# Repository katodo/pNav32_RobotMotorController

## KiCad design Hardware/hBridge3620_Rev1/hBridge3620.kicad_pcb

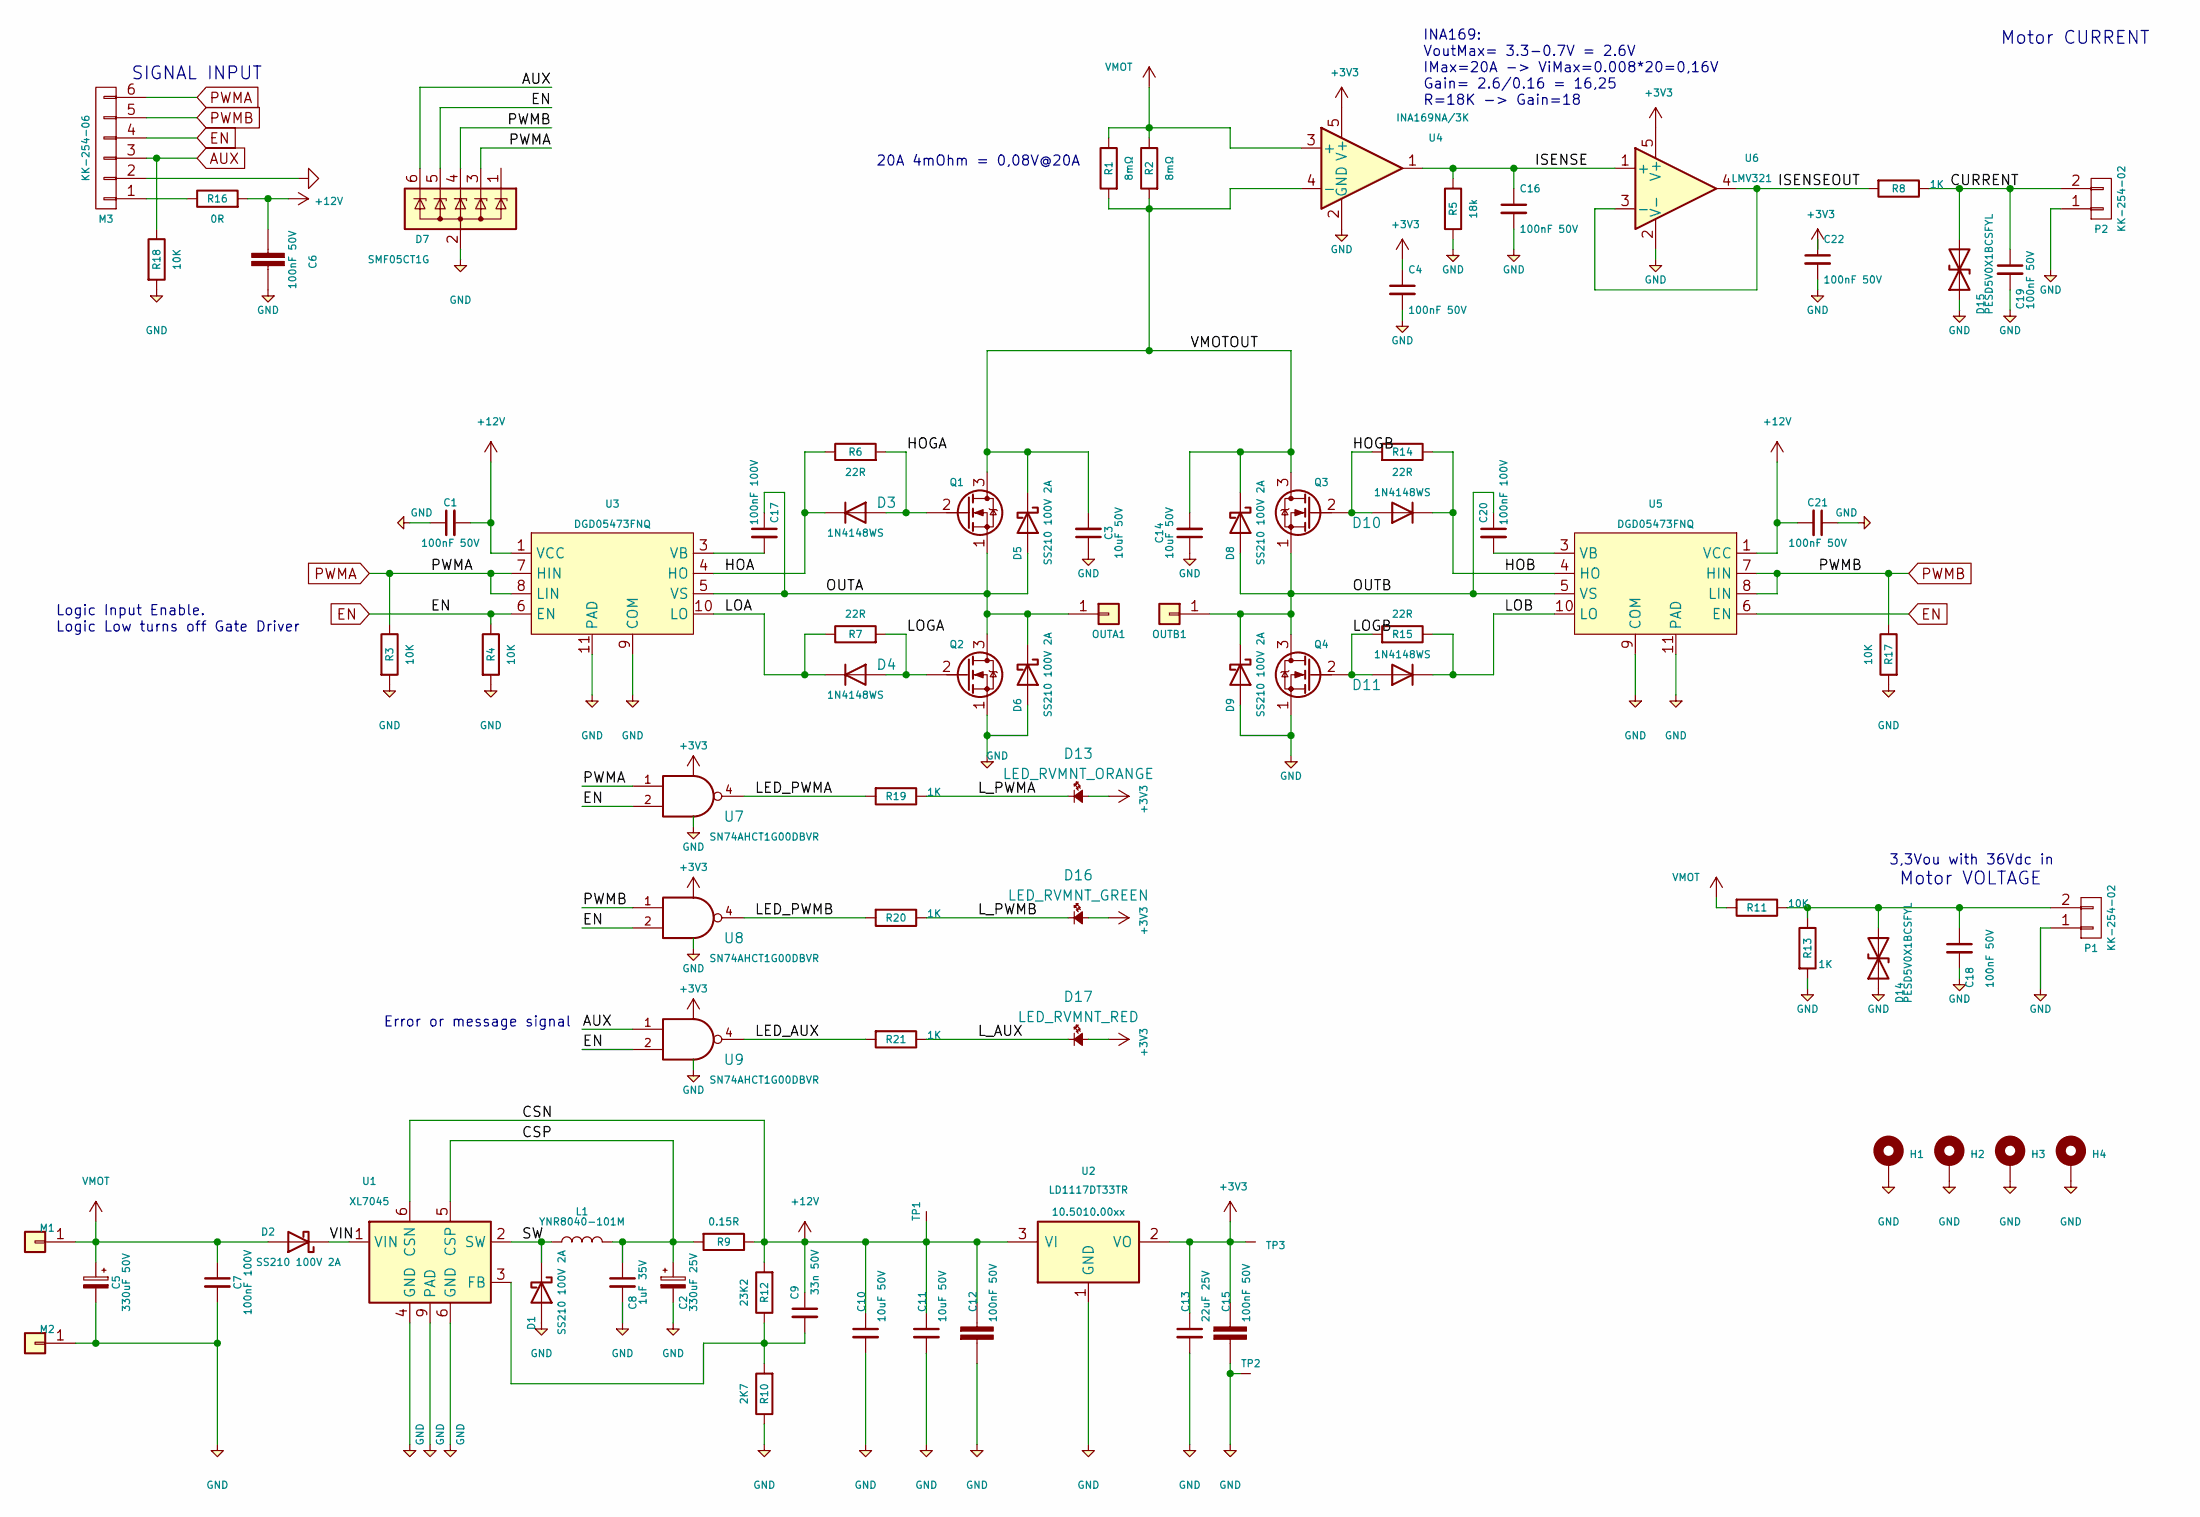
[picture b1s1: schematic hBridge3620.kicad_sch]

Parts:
C1, C4, C6, C12, C15, C16, C18, C19, C21, C22: 100nF 50V; C_0603_1608Metric; LCSC C14663
C2: 330uF 25V; CP_Radial_D10.0mm_P5.00mm
C3, C10, C11, C14: 10uF 50V; C_1206_3216Metric_Pad1.33x1.80mm_HandSolder; LCSC C13585
C5: 330uF 50V; CP_Radial_D12.5mm_P5.00mm
C7, C17, C20: 100nF 100V; C_0805_2012Metric; LCSC C28233
C8: 1uF 35V; C_0805_2012Metric; LCSC C28323
C9: 33n 50V; C_0603_1608Metric; LCSC C21117
C13: 22uF 25V; C_1206_3216Metric_Pad1.33x1.80mm_HandSolder; LCSC C12891
D1, D2, D5, D6, D8, D9: SS210 100V 2A; D_SMA; LCSC C14996
D3, D4, D10, D11: 1N4148WS; D_SOD-323; LCSC C2128
D7: SMF05CT1G; SOT-363_SC-70-6; LCSC C15879
D13: LED_RVMNT_ORANGE; LED_1206_3216Metric_ReverseMount_Hole1.8x2.4mm; MOUSER 859-LTST-C230KFKT
D14, D15: PESD5V0X1BCSFYL; D_0603_1608Metric; LCSC C2443412
D16: LED_RVMNT_GREEN; LED_1206_3216Metric_ReverseMount_Hole1.8x2.4mm; MOUSER 859-LTST-C230KGKT
D17: LED_RVMNT_RED; LED_1206_3216Metric_ReverseMount_Hole1.8x2.4mm; MOUSER 859-LTST-C230KRKT
H1, H2, H3, H4: MountingHole_Pad; MountingHole_3.2mm_M3_Pad_Via
L1: YNR8040-101M; L_Taiyo-Yuden_NR-80xx; LCSC C341083
M1, M2: HIGHCURRENTPAD2; SolderWire-2.5sqmm_1x01_D2.4mm_OD4.4mm
M3: KK-254-06; Molex_KK-254_AE-6410-06A_1x06_P2.54mm_Vertical
OUTA1: HIGHCURRENTPAD2; SolderWire-2.5sqmm_1x01_D2.4mm_OD4.4mm
OUTB1: HIGHCURRENTPAD2; SolderWire-2.5sqmm_1x01_D2.4mm_OD4.4mm
P1, P2: KK-254-02; Molex_KK-254_AE-6410-02A_1x02_P2.54mm_Vertical
Q1, Q2, Q3, Q4: RU6888M; DFN-8-1EP_5.55x5.2mm_P1.27mm_EP4.12x4.6mm_MOSFET_3PIN; LCSC C180959
R1, R2: 8mΩ; R_2512_6332Metric; LCSC C469375
R3, R4, R11, R17, R18: 10K; R_0603_1608Metric; LCSC C25804
R5: 18k; R_0603_1608Metric; LCSC C25810
R6, R7, R14, R15: 22R; R_0603_1608Metric; LCSC C23345
R8, R13, R19, R20, R21: 1K; R_0603_1608Metric; LCSC C21190
R9: 0.15R; R_1206_3216Metric; LCSC C37936
R10: 2K7; R_0603_1608Metric; LCSC C13167
R12: 23K2; R_0603_1608Metric; LCSC C2930078
R16: 0R; R_0603_1608Metric; LCSC C21189
TP1, TP2, TP3: TESTPAD; TestPoint_Pad_2.5x2.5mm
U1: XL7045; SOIC-8-1EP_3.9x4.9mm_P1.27mm_EP2.29x3mm; LCSC C126474
U2: LD1117DT33TR; TO-252-2; LCSC C36395
U3, U5: DGD05473FNQ; U-DFN3030-10_3.1x3.1mm_P0.5mm_EP1.8x2.6mm_ThermalVias; LCSC C2677131
U4: INA169NA/3K; SOT-23-5; LCSC C44322
U6: LMV321; SOT-23-5; LCSC C7972
U7, U8, U9: SN74AHCT1G00DBVR; SOT-23-5; LCSC C473380

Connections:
+3V3: C4.1, C13.1, C15.1, C22.1, D13.2, D16.2, D17.2, TP3.1 (TP), U2.2 (VO), U4.5 (V+), U6.5 (V+), U7.5 (VCC), U8.5 (VCC), U9.5 (VCC)
/CSP: C2.1, C8.1, L1.2, R9.2, U1.5 (CSP)
/CURRENT: C19.1, D15.2 (A2), P2.2, R8.1
/HOA: D3.1 (K), R6.1, U3.4 (HO)
/HOB: D10.1 (K), R14.1, U5.4 (HO)
/HOGA: D3.2 (A), Q1.2 (G), R6.2
/HOGB: D10.2 (A), Q3.2 (G), R14.2
/ISENSE: C16.1, R5.1, U4.1, U6.1 (+)
/ISENSEOUT: R8.2, U6.3 (-), U6.4
/LED_AUX: R21.2, U9.4
/LED_PWMA: R19.2, U7.4
/LED_PWMB: R20.2, U8.4
/LOA: D4.1 (K), R7.1, U3.10 (LO)
/LOB: D11.1 (K), R15.1, U5.10 (LO)
/LOGA: D4.2 (A), Q2.2 (G), R7.2
/LOGB: D11.2 (A), Q4.2 (G), R15.2
/L_AUX: D17.1, R21.1
/L_PWMA: D13.1, R19.1
/L_PWMB: D16.1, R20.1
/OUTA: C17.1, D5.2 (A), D6.1 (K), OUTA1.1, Q1.1 (S), Q2.3 (D), U3.5 (VS)
/OUTB: C20.1, D8.2 (A), D9.1 (K), OUTB1.1, Q3.1 (S), Q4.3 (D), U5.5 (VS)
/SW: D1.1 (K), L1.1, U1.2 (SW)
/VIN: D2.1 (K), U1.1 (VIN)
/VMOTOUT: C3.2, C14.2, D5.1 (K), D8.1 (K), Q1.3 (D), Q3.3 (D), R1.2, R2.2, U4.4 (-)
AUX: D7.6 (K), M3.3, R18.1, U9.1
EN: D7.5 (K), M3.4, R4.1, U3.6 (EN), U5.6 (EN), U7.2, U8.2, U9.2
unnamed: C9.2, R10.2, R12.1, U1.3 (FB)
unnamed: C17.2, U3.3 (VB)
unnamed: C18.1, D14.2 (A2), P1.2, R11.1, R13.1
unnamed: C20.2, U5.3 (VB)
unnamed: M3.1, R16.1
PWMA: D7.3 (K), M3.6, R3.1, U3.7 (HIN), U3.8 (LIN), U7.1
PWMB: D7.4 (K), M3.5, R17.1, U5.7 (HIN), U5.8 (LIN), U8.1
VMOT: C5.1, C7.1, D2.2 (A), M1.1, R1.1, R2.1, R11.2, U4.3 (+)

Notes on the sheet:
3,3Vou with 36Vdc in
Logic Input Enable. Logic Low turns off Gate Driver
Motor VOLTAGE
Motor CURRENT
20A 4mOhm = 0,08V@20A
INA169: VoutMax= 3.3-0.7V = 2.6V IMax=20A -> ViMax=0.008*20=0,16V Gain= 2.6/0.16 = 16,25 R=18K -> Gain=18
Error or message signal
SIGNAL INPUT

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
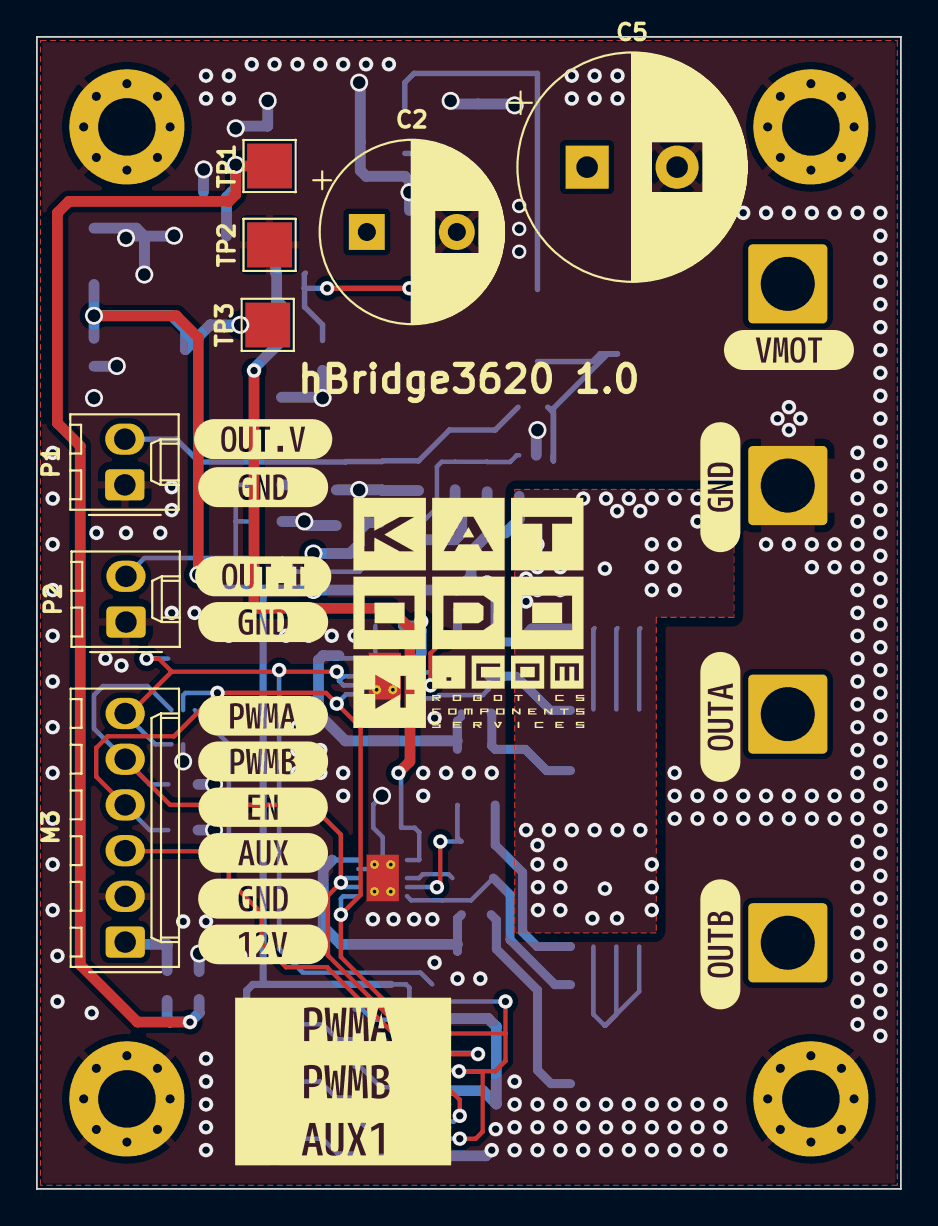
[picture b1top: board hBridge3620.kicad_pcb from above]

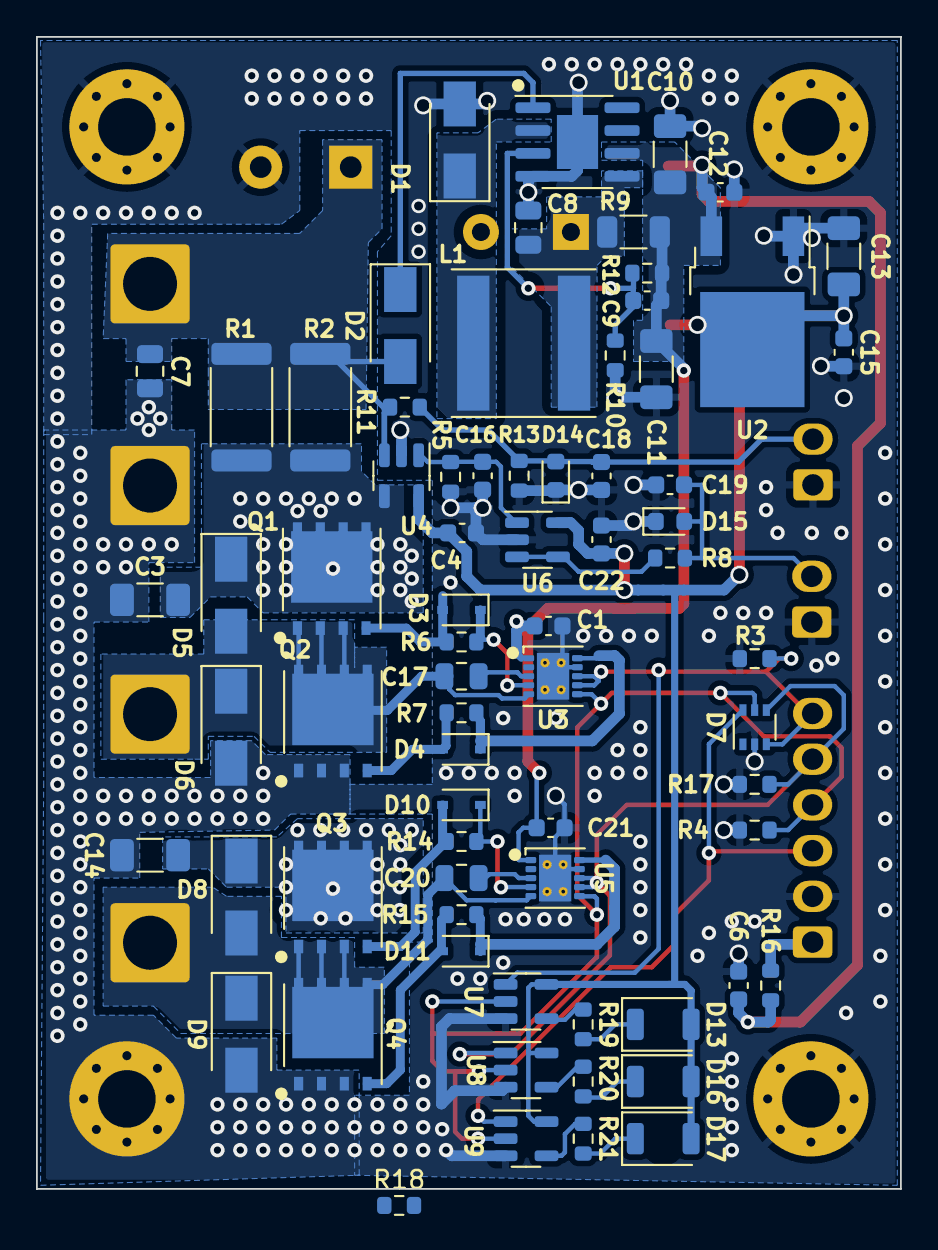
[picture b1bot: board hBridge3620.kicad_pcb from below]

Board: 2 copper layers, 48.0 x 64.0 mm, 102 parts (71 on the bottom side), 36 nets.

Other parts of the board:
kibuzzard-63AF517B: G***; kibuzzard-63AF517B
kibuzzard-63AF5189: G***; kibuzzard-63AF5189
kibuzzard-63B18A56: G***; kibuzzard-63B18A56
kibuzzard-63B18C51: G***; kibuzzard-63B18C51
kibuzzard-63B18C79: G***; kibuzzard-63B18C79
kibuzzard-63B18C86: G***; kibuzzard-63B18C86
kibuzzard-63B83704: G***; kibuzzard-63B83704
kibuzzard-63934BD9, kibuzzard-63934BD9#2, kibuzzard-63934BD9#3: G***; kibuzzard-63934BD9
kibuzzard-6393473F: G***; kibuzzard-6393473F
kibuzzard-63934735: G***; kibuzzard-63934735
kibuzzard-63934749: G***; kibuzzard-63934749
kibuzzard-63934750: G***; kibuzzard-63934750
kibuzzard-63934760: G***; kibuzzard-63934760

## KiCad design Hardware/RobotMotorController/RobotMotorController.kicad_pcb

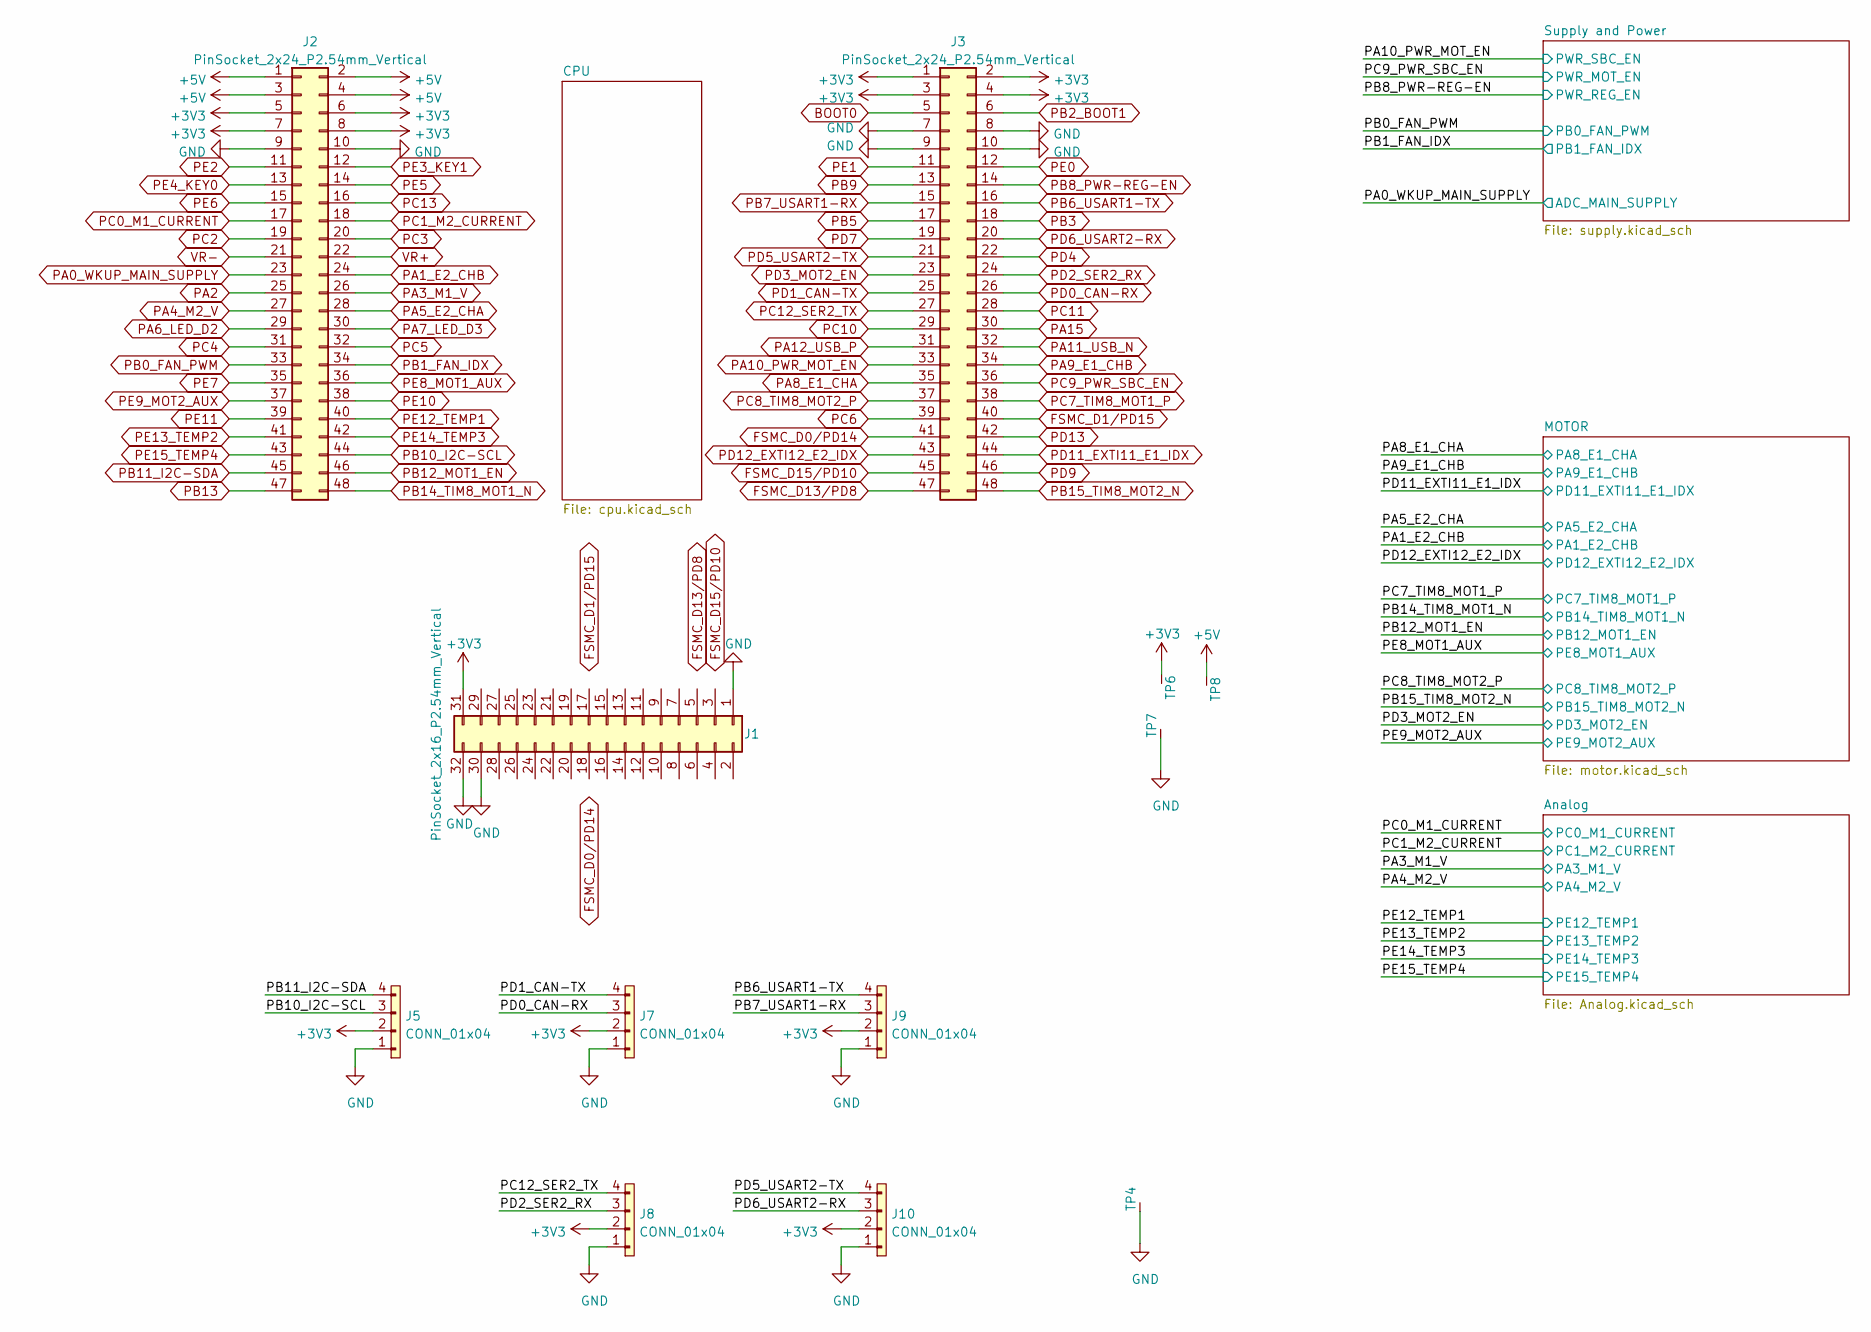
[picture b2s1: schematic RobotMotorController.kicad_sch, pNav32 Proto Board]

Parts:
J1: PinSocket_2x16_P2.54mm_Vertical
J2, J3: PinSocket_2x24_P2.54mm_Vertical
J5, J7, J8, J9, J10: CONN_01x04; Molex_KK-254_AE-6410-04A_1x04_P2.54mm_Vertical
TP4, TP6, TP7, TP8: TESTPAD; TestPoint_Loop_D2.50mm_Drill1.85mm

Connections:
+3V3: J1.31, J2.5, J2.6, J2.7, J2.8, J3.1, J3.2, J3.3, J3.4, J5.2, J7.2, J8.2, J9.2, J10.2, TP6.1 (TP); also elsewhere on the board
+5V: J2.1, J2.2, J2.3, J2.4, TP8.1 (TP); also elsewhere on the board
BOOT0: J3.5
FSMC_D0/PD14: J3.41
FSMC_D1/PD15: J3.40
FSMC_D13/PD8: J3.47
FSMC_D15/PD10: J3.45
PA0_WKUP_MAIN_SUPPLY: J2.23; also elsewhere on the board
PA1_E2_CHB: J2.24; also elsewhere on the board
PA2: J2.25
PA3_M1_V: J2.26; also elsewhere on the board
PA4_M2_V: J2.27; also elsewhere on the board
PA5_E2_CHA: J2.28; also elsewhere on the board
PA6_LED_D2: J2.29
PA7_LED_D3: J2.30
PA8_E1_CHA: J3.35; also elsewhere on the board
PA9_E1_CHB: J3.34; also elsewhere on the board
PA10_PWR_MOT_EN: J3.33; also elsewhere on the board
PA11_USB_N: J3.32
PA12_USB_P: J3.31
PA15: J3.30
PB0_FAN_PWM: J2.33; also elsewhere on the board
PB1_FAN_IDX: J2.34; also elsewhere on the board
PB2_BOOT1: J3.6
PB3: J3.18
PB5: J3.17
PB6_USART1-TX: J3.16, J9.4
PB7_USART1-RX: J3.15, J9.3
PB8_PWR-REG-EN: J3.14; also elsewhere on the board
PB9: J3.13
PB10_I2C-SCL: J2.44, J5.3
PB11_I2C-SDA: J2.45, J5.4
PB12_MOT1_EN: J2.46; also elsewhere on the board
PB13: J2.47
PB14_TIM8_MOT1_N: J2.48; also elsewhere on the board
PB15_TIM8_MOT2_N: J3.48; also elsewhere on the board
PC0_M1_CURRENT: J2.17; also elsewhere on the board
PC1_M2_CURRENT: J2.18; also elsewhere on the board
PC2: J2.19
PC3: J2.20
PC4: J2.31
PC5: J2.32
PC6: J3.39
PC7_TIM8_MOT1_P: J3.38; also elsewhere on the board
PC8_TIM8_MOT2_P: J3.37; also elsewhere on the board
PC9_PWR_SBC_EN: J3.36; also elsewhere on the board
PC10: J3.29
PC11: J3.28
PC12_SER2_TX: J3.27, J8.4
PC13: J2.16
PD0_CAN-RX: J3.26, J7.3
PD1_CAN-TX: J3.25, J7.4
PD2_SER2_RX: J3.24, J8.3
PD3_MOT2_EN: J3.23; also elsewhere on the board
PD4: J3.22
PD5_USART2-TX: J3.21, J10.4
PD6_USART2-RX: J3.20, J10.3
PD7: J3.19
PD9: J3.46
PD11_EXTI11_E1_IDX: J3.44; also elsewhere on the board
PD12_EXTI12_E2_IDX: J3.43; also elsewhere on the board
PD13: J3.42
PE0: J3.12
PE1: J3.11
PE2: J2.11
PE3_KEY1: J2.12
PE4_KEY0: J2.13
PE5: J2.14
PE6: J2.15
PE7: J2.35
PE8_MOT1_AUX: J2.36; also elsewhere on the board
PE9_MOT2_AUX: J2.37; also elsewhere on the board
PE10: J2.38
PE11: J2.39
PE12_TEMP1: J2.40; also elsewhere on the board
PE13_TEMP2: J2.41; also elsewhere on the board
PE14_TEMP3: J2.42; also elsewhere on the board
PE15_TEMP4: J2.43; also elsewhere on the board
VR+: J2.22
VR-: J2.21

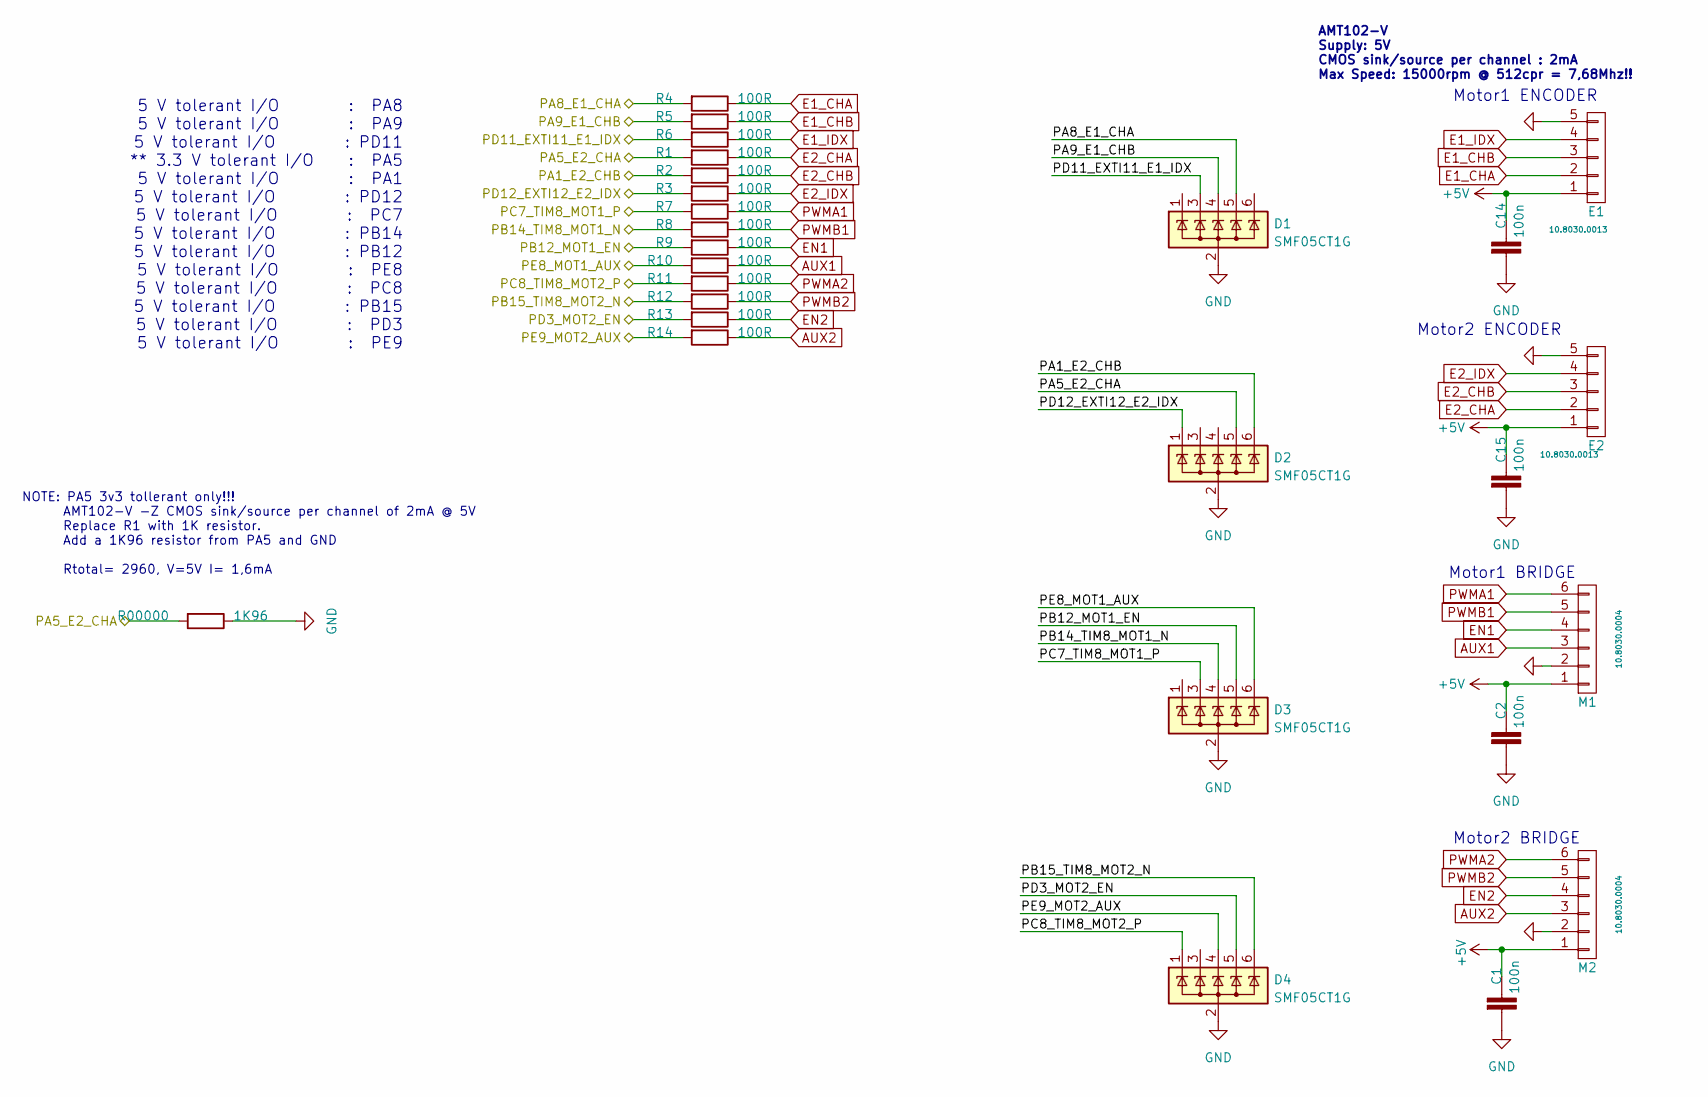
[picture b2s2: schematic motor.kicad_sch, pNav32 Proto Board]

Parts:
C1, C2, C14, C15: 100n; C_0603_1608Metric; LCSC C14663
D1, D2, D3, D4: SMF05CT1G; SOT-363_SC-70-6; LCSC C15879
E1, E2: Molex_KK-254_AE-6410-05A_1x05_P2.54mm_Vertical
M1, M2: Molex_KK-254_AE-6410-06A_1x06_P2.54mm_Vertical
R00000: 1K96; R_0603_1608Metric; LCSC C227664
R1: 100R; R_0603_1608Metric; LCSC C21190
R2, R3, R4, R5, R6, R7, R8, R9, R10, R11, R12, R13, R14: 100R; R_0603_1608Metric; LCSC C22775

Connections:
+5V: C1.1, C2.1, C14.1, C15.1, E1.1, E2.1, M1.1, M2.1; also elsewhere on the board
AUX1: M1.3, R10.1
AUX2: M2.3, R14.1
E1_CHA: E1.2, R4.1
E1_CHB: E1.3, R5.1
E1_IDX: E1.4, R6.1
E2_CHA: E2.2, R1.1
E2_CHB: E2.3, R2.1
E2_IDX: E2.4, R3.1
EN1: M1.4, R9.1
EN2: M2.4, R13.1
PA1_E2_CHB: D2.6 (K), R2.2; also elsewhere on the board
PA5_E2_CHA: D2.5 (K), R00000.2, R1.2; also elsewhere on the board
PA8_E1_CHA: D1.5 (K), R4.2; also elsewhere on the board
PA9_E1_CHB: D1.4 (K), R5.2; also elsewhere on the board
PB12_MOT1_EN: D3.5 (K), R9.2; also elsewhere on the board
PB14_TIM8_MOT1_N: D3.4 (K), R8.2; also elsewhere on the board
PB15_TIM8_MOT2_N: D4.6 (K), R12.2; also elsewhere on the board
PC7_TIM8_MOT1_P: D3.3 (K), R7.2; also elsewhere on the board
PC8_TIM8_MOT2_P: D4.1 (K), R11.2; also elsewhere on the board
PD3_MOT2_EN: D4.5 (K), R13.2; also elsewhere on the board
PD11_EXTI11_E1_IDX: D1.3 (K), R6.2; also elsewhere on the board
PD12_EXTI12_E2_IDX: D2.1 (K), R3.2; also elsewhere on the board
PE8_MOT1_AUX: D3.6 (K), R10.2; also elsewhere on the board
PE9_MOT2_AUX: D4.4 (K), R14.2; also elsewhere on the board
PWMA1: M1.6, R7.1
PWMA2: M2.6, R11.1
PWMB1: M1.5, R8.1
PWMB2: M2.5, R12.1

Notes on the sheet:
Motor1 ENCODER
Motor2 ENCODER
Motor2 BRIDGE
5 V tolerant I/O : PA8 5 V tolerant I/O : PA9 5 V tolerant I/O : PD11 ** 3.3 V tolerant I/O : PA5 5 V tolerant I/O : PA1 5 V tolerant I/O : PD12 5 V tolerant I/O : PC7 5 V tolerant I/O : PB14 5 V tolerant I/O : PB12 5 V tolerant I/O : PE8 5 V tolerant I/O : PC8 5 V tolerant I/O : PB15 5 V tolerant 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
NOTE: PA5 3v3 tollerant only!!! AMT102-V -Z CMOS sink/source per channel of 2mA @ 5V Replace R1 with 1K resistor. Add a 1K96 resistor from PA5 and GND Rtotal= 2960, V=5V I= 1,6mA
Motor1 BRIDGE
AMT102-V Supply: 5V CMOS sink/source per channel : 2mA Max Speed: 15000rpm @ 512cpr = 7,68Mhz!!

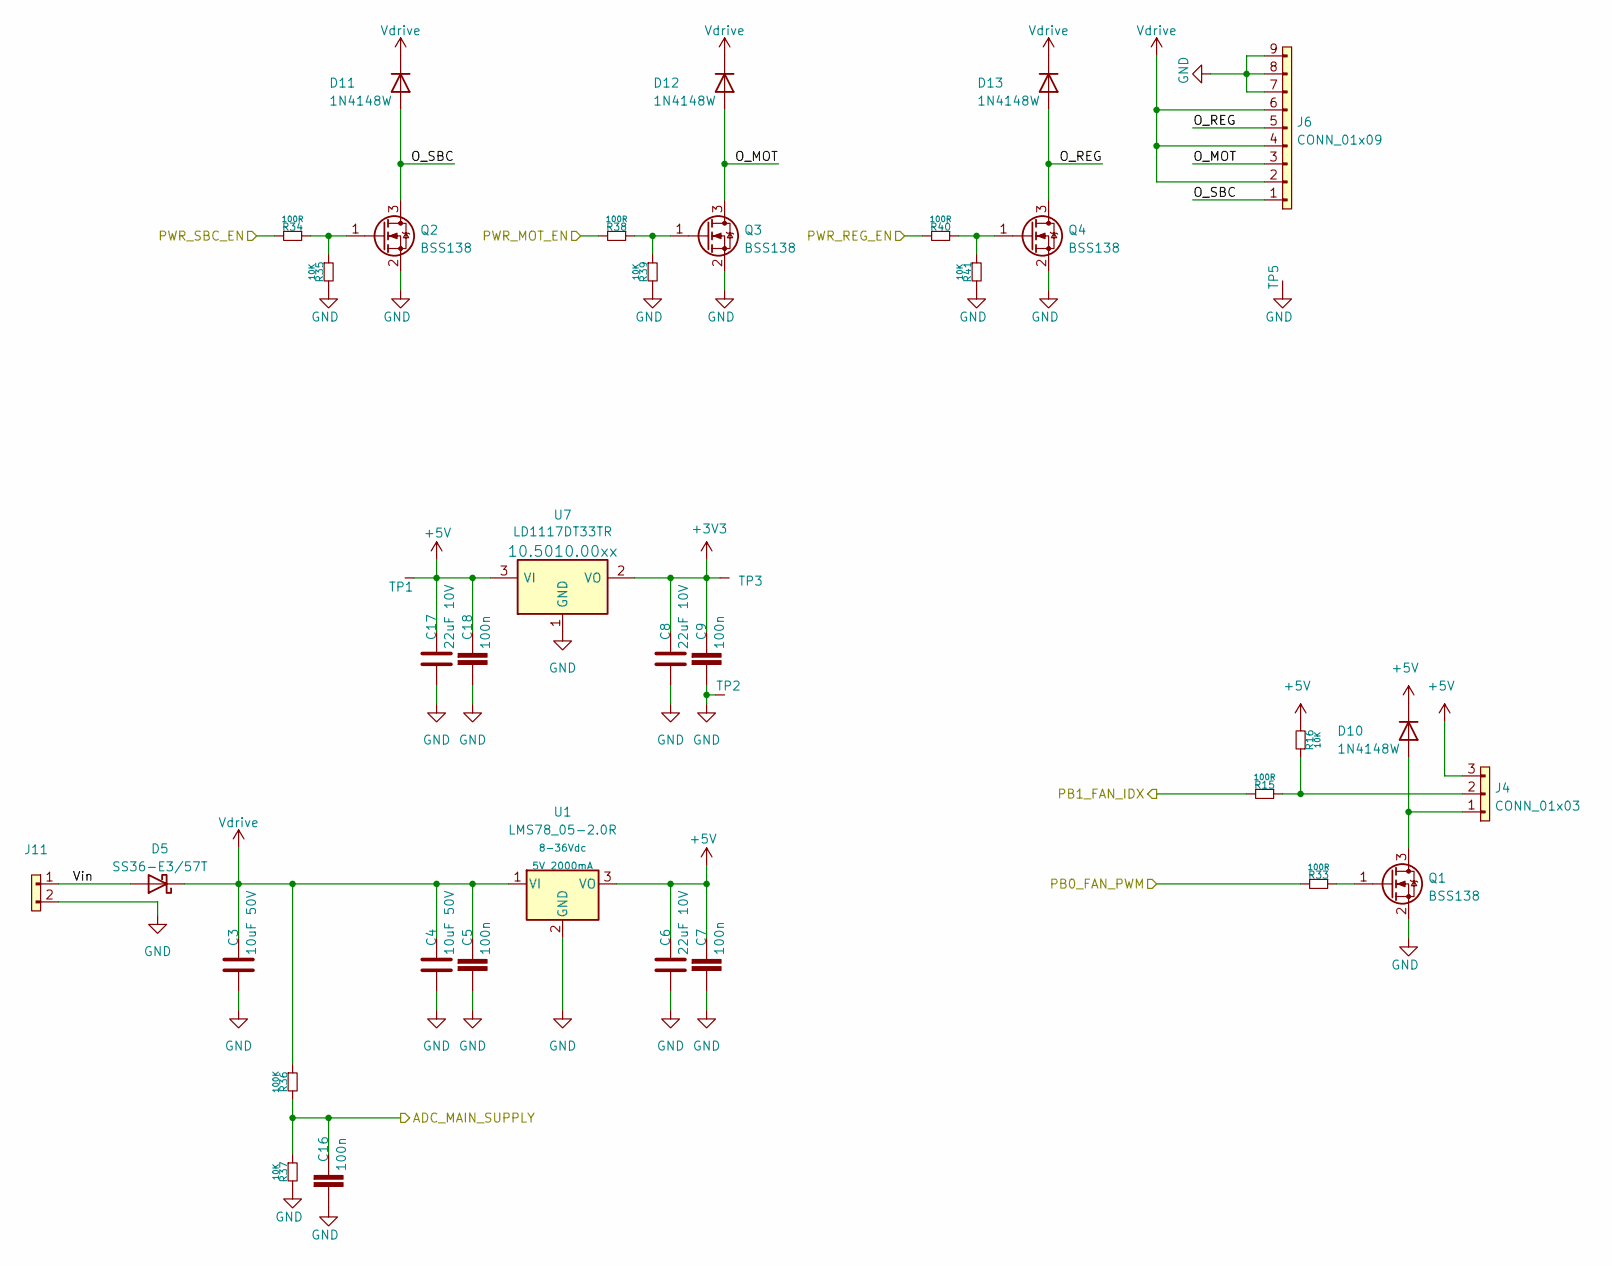
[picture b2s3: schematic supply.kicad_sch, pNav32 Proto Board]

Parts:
C3, C4: 10uF 50V; C_1206_3216Metric_Pad1.33x1.80mm_HandSolder; DIGIKEY 1276-6736-1-ND
C5, C7, C9, C16, C18: 100n; C_0603_1608Metric; LCSC C14663
C6, C8, C17: 22uF 10V; C_1206_3216Metric_Pad1.33x1.80mm_HandSolder; LCSC C12891
D5: SS36-E3/57T; D_SMC; LCSC C35722
D10, D11, D12, D13: 1N4148W; D_SOD-123; LCSC C81598
J4: CONN_01x03; Molex_KK-254_AE-6410-03A_1x03_P2.54mm_Vertical
J6: CONN_01x09; DG300-5.0-09P-13
J11: dG300-5.0-02P-13-00AH; DG300-5.0-02P-13
Q1, Q2, Q3, Q4: BSS138; SOT-23; LCSC C255592
R15, R33, R34, R38, R40: 100R; R_0603_1608Metric; MPN CRCW06031K00FKEA; FARNELL 2122366
R16, R35, R37, R39, R41: 10K; R_0603_1608Metric; MPN CRCW06031K00FKEA; FARNELL 2122366
R36: 100K; R_0603_1608Metric; MPN CRCW06031K00FKEA; FARNELL 2122366
TP1, TP2, TP3: TESTPAD; TestPoint_Pad_2.5x2.5mm
TP5: TESTPAD; TestPoint_Loop_D2.50mm_Drill1.85mm
U1: LMS78_05-2.0R; SIP3_11.6x8.5mm; LCSC C2931187
U7: LD1117DT33TR; TO-252-2; LCSC C132629

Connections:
+3V3: C8.1, C9.1, TP3.1 (TP), U7.2 (VO); also elsewhere on the board
+5V: C6.1, C7.1, C17.1, C18.1, D10.1 (K), J4.3, R16.2, TP1.1 (TP), U1.3 (VO), U7.3 (VI); also elsewhere on the board
/Supply and Power/O_MOT: D12.2 (A), J6.3, Q3.3 (D)
/Supply and Power/O_REG: D13.2 (A), J6.5, Q4.3 (D)
/Supply and Power/O_SBC: D11.2 (A), J6.1, Q2.3 (D)
/Supply and Power/Vin: D5.2 (A), J11.1
unnamed: D10.2 (A), J4.1, Q1.3 (D)
unnamed: J4.2, R15.1, R16.1
unnamed: Q1.1 (G), R33.1
unnamed: Q2.1 (G), R34.1, R35.1
unnamed: Q3.1 (G), R38.1, R39.1
unnamed: Q4.1 (G), R40.1, R41.1
PA0_WKUP_MAIN_SUPPLY: C16.1, R36.2, R37.1; also elsewhere on the board
PA10_PWR_MOT_EN: R34.2; also elsewhere on the board
PB0_FAN_PWM: R33.2; also elsewhere on the board
PB1_FAN_IDX: R15.2; also elsewhere on the board
PB8_PWR-REG-EN: R40.2; also elsewhere on the board
PC9_PWR_SBC_EN: R38.2; also elsewhere on the board
Vdrive: C3.1, C4.1, C5.1, D5.1 (K), D11.1 (K), D12.1 (K), D13.1 (K), J6.2, J6.4, J6.6, R36.1, U1.1 (VI)
